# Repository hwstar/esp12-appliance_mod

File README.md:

**esp12-appliance_mod**
==========
This is a hardware implementation for my ESP8266-MQTT-io-node project.

**Features:**

Provides one bistable latching relay channel. Connectors are provided for a link LED and a local button to latch and unlatch the relay.
A dual voltage isolated power supply mounts over the top of the latching relay. The relay is capable of switching  a 16 Amp resistive load at 250VAC, or
a 20 Amp resistive load at 125VAC. See relay data sheet for further details. There are screw terminals for attaching the AC wiring  at the rear of the board (behind the power supply).

**EDA Software**

This board was designed using KICAD. 

**Board Size**

10cm x 10cm

**Board Blank Availability**

Board Blanks are available on Tindie:

https://www.tindie.com/products/hwstarsr/board-blank-for-esp12-appliancemod

**Firmware**

The firmware for this project can be found here:

https://github.com/hwstar/ESP8266-MQTT-io-node

**LICENSE**

Creative Commons Attribution Share-Alike license. (CC-BY-SA)

**Disclaimer**

Build and use at your own risk. This board design uses lethal mains voltages. I will not be responsible for any damages including but not limited to: errors or omissions, loss of life, or property damage. You have been warned.

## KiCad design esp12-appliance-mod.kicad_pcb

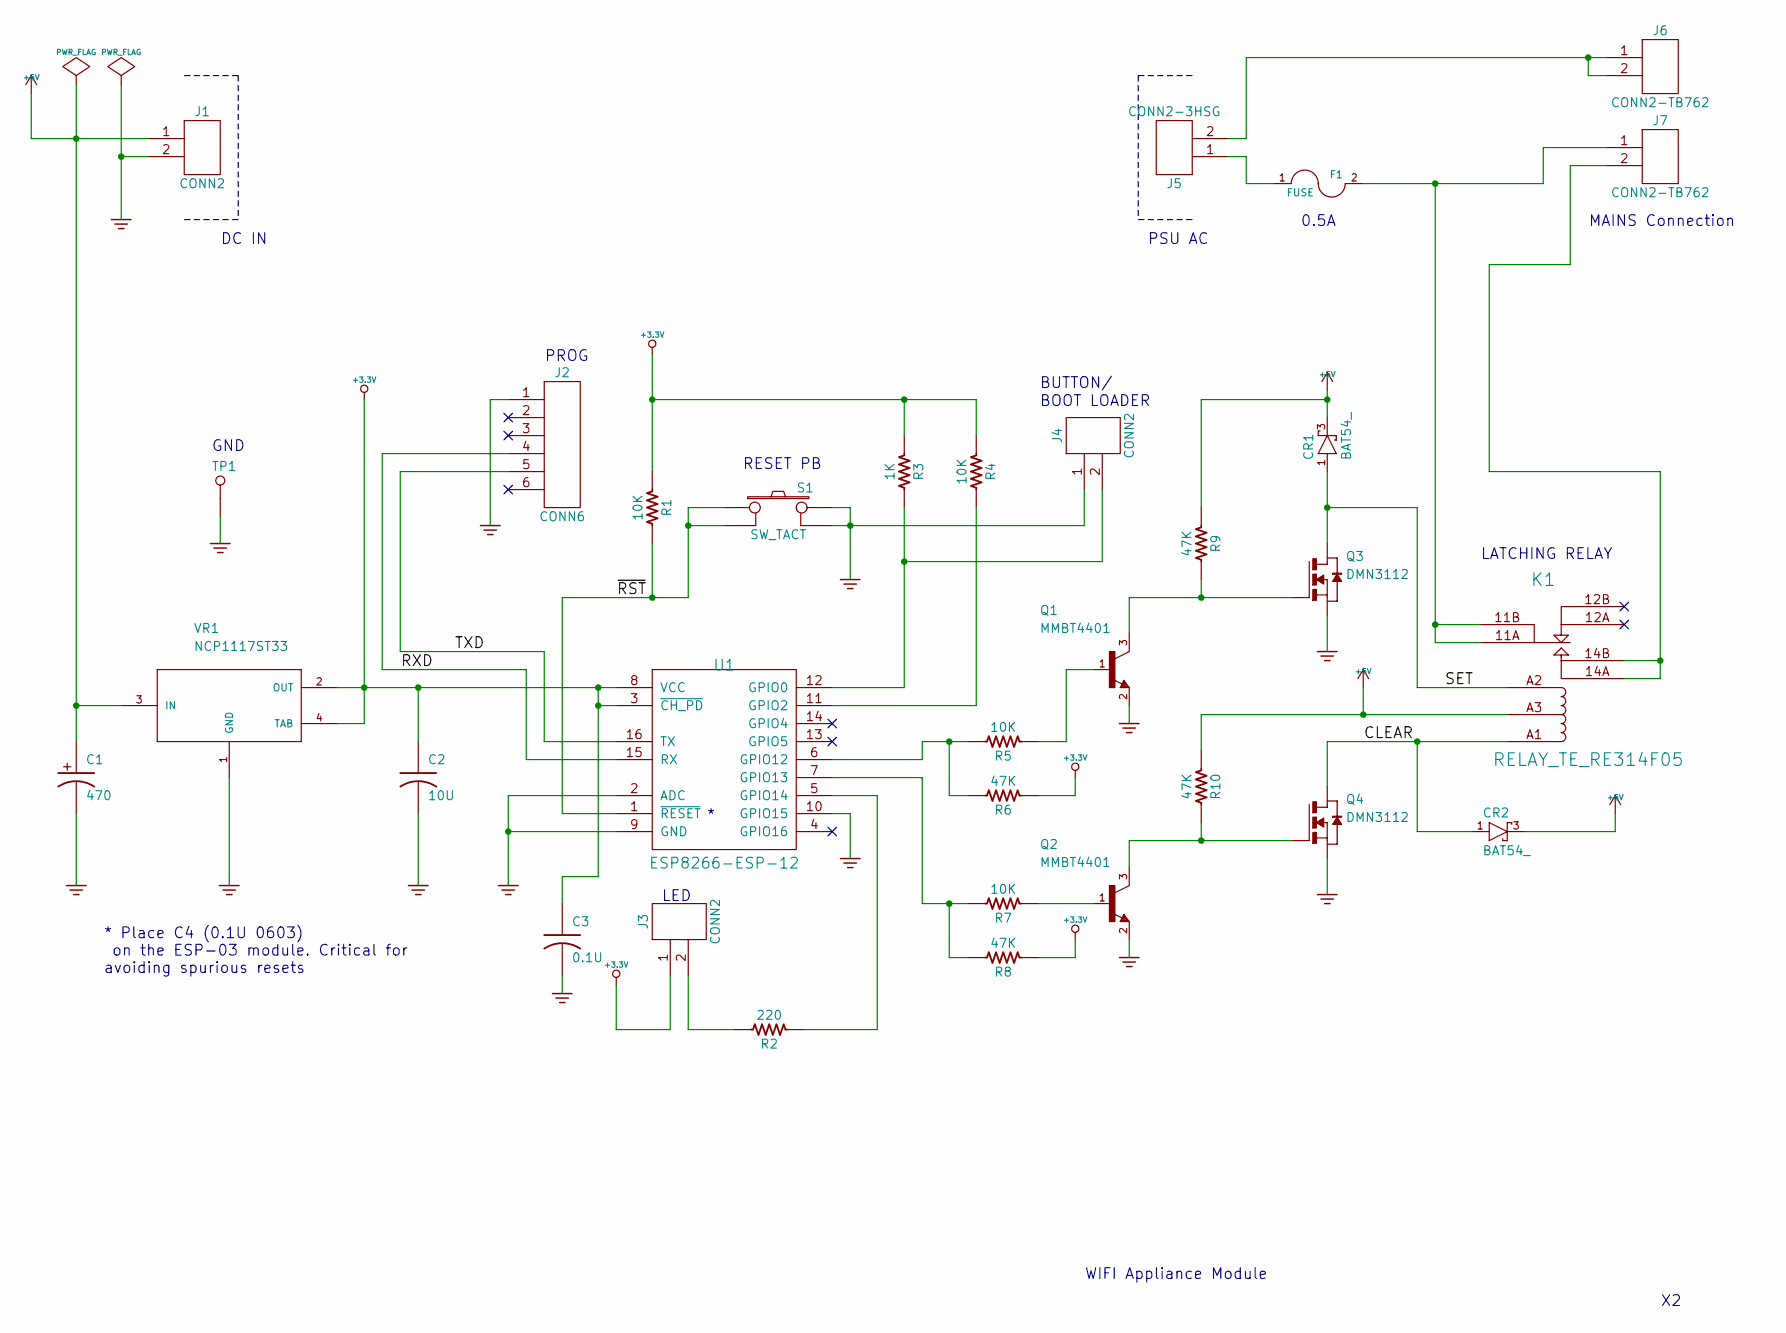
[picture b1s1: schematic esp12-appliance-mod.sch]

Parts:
C1: 470; PartNumber 800126-477
C2: 10U; CC0805; PartNumber 800003-106
C3: 0.1U; PartNumber 800000-104
CR1, CR2: BAT54_; SOT23; PartNumber 800127-101
F1: FUSE; PartNumber 800125-500
J1, J3, J4: CONN2; PartNumber 800114-102
J2: CONN6; PartNumber 800116-106
J5: CONN2-3HSG; PartNumber 800124-101
J6, J7: CONN2-TB762; PartNumber 800129-102
K1: RELAY_TE_RE314F05; PartNumber 800128-101
Q1, Q2: MMBT4401; SOT23; PartNumber 800110-101
Q3, Q4: DMN3112; SOT23; PartNumber 800123-101
R1, R4, R5, R7: 10K; RC0603; PartNumber 800010-103
R2: 220; RC0805; PartNumber 800011-221
R3: 1K; RC0603; PartNumber 800010-102
R6, R8, R9: 47K; RC0603; PartNumber 800010-473
R10: 47K; RC0603
S1: SW_TACT; PartNumber 800107-101
TP1: TESTPINTPSQ025; TESTPINSQ025
U1: ESP8266-ESP-12; PartNumber 800106-101
VR1: NCP1117ST33; SOT223; PartNumber 800121-101

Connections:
+3.3V: C2.1, C3.1, J3.1, R1.1, R3.1, R4.1, R6.1, R8.1, U1.3 (~CH_PD), U1.8 (VCC), VR1.2 (OUT), VR1.4 (TAB)
+5V: C1.1, CR1.3 (C), CR2.3 (C), J1.1, K1.A3, R9.1, R10.1, VR1.3 (IN)
/CLEAR: CR2.1 (A), K1.A1 (RESET), Q4.3 (D)
/RXD: J2.4, U1.15 (RX)
/SET: CR1.1 (A), K1.A2 (SET), Q3.3 (D)
/TXD: J2.5, U1.16 (TX)
/~RST: R1.2, S1.1, S1.2, U1.1 (~RESET)
GND: C1.2, C2.2, C3.2, J1.2, J2.1, J4.1, Q1.2 (E), Q2.2 (E), Q3.2 (S), Q4.2 (S), S1.3, S1.4, TP1.1, U1.2 (ADC), U1.9 (GND), U1.10 (GPIO15), VR1.1 (GND)
unnamed: F1.1, J5.1
unnamed: F1.2, J7.1, K1.11A (C), K1.11B (C)
unnamed: J3.2, R2.2
unnamed: J4.2, R3.2, U1.12 (GPIO0)
unnamed: J5.2, J6.1, J6.2
unnamed: J7.2, K1.14A (NO), K1.14B (NO)
unnamed: Q1.1 (B), R5.1
unnamed: Q1.3 (C), Q3.1 (G), R9.2
unnamed: Q2.1 (B), R7.1
unnamed: Q2.3 (C), Q4.1 (G), R10.2
unnamed: R2.1, U1.5 (GPIO14)
unnamed: R4.2, U1.11 (GPIO2)
unnamed: R5.2, R6.2, U1.6 (GPIO12)
unnamed: R7.2, R8.2, U1.7 (GPIO13)

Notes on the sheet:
RESET PB
BOOT LOADER
WIFI Appliance Module
LED
DC IN
0.5A
* Place C4 (0.1U 0603) on the ESP-03 module. Critical for avoiding spurious resets
MAINS Connection
PSU AC
BUTTON/
PROG
LATCHING RELAY
GND

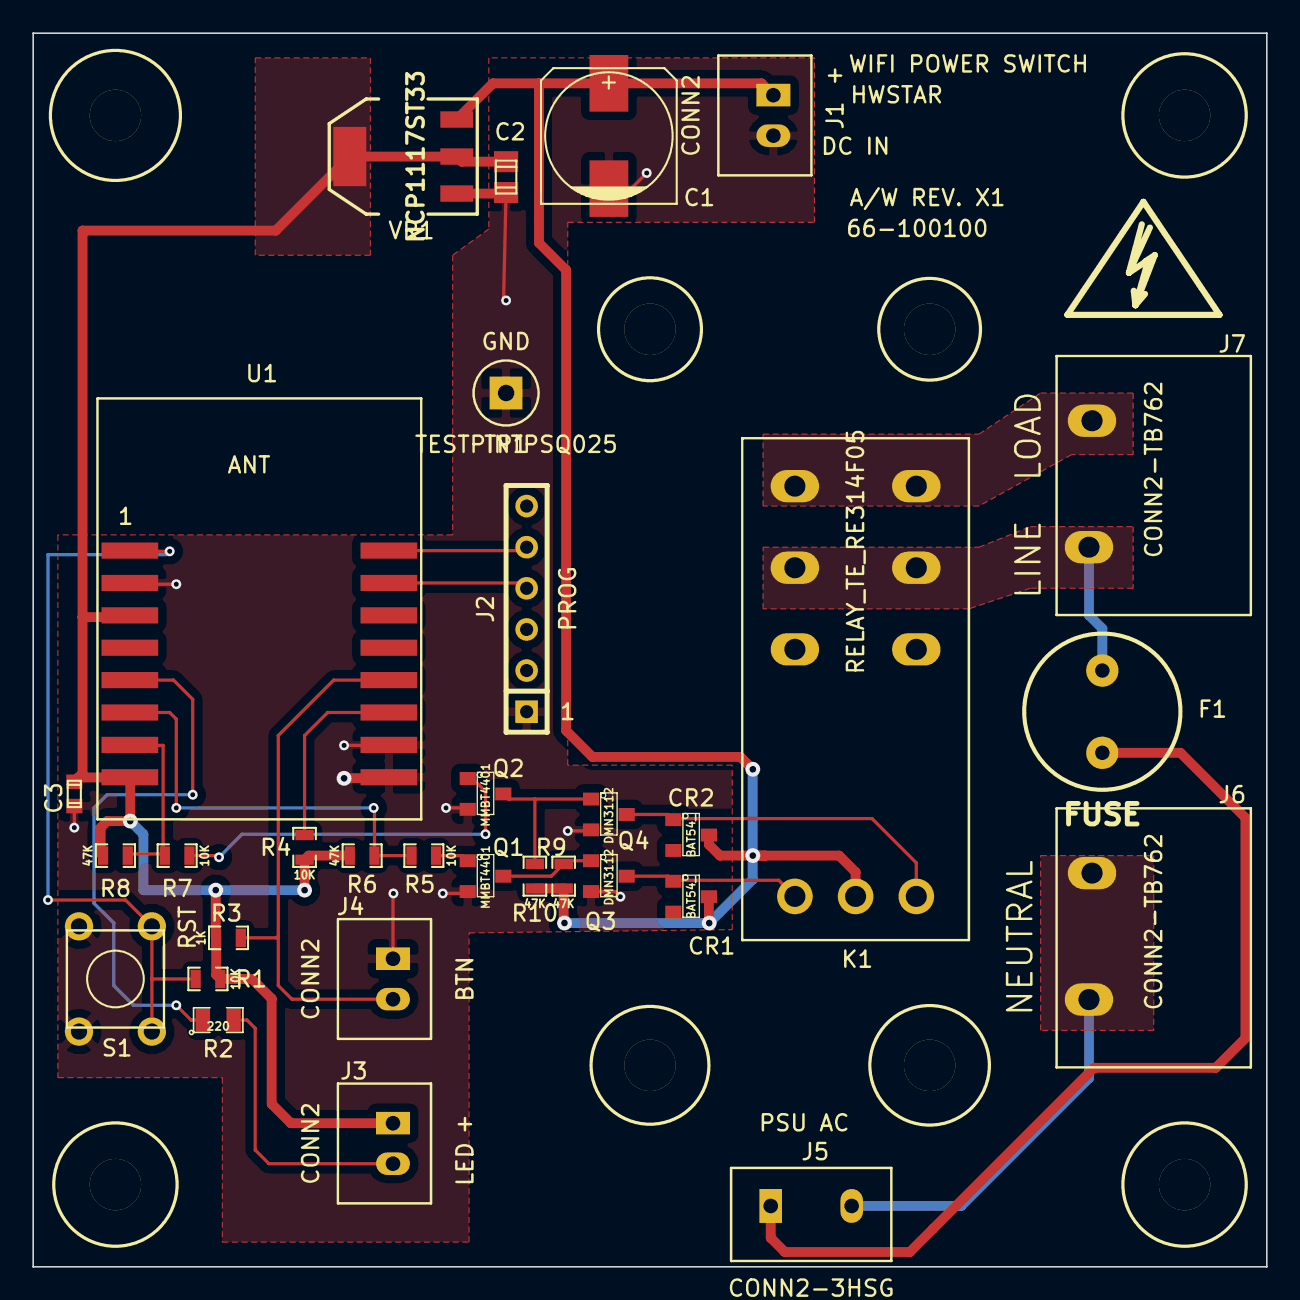
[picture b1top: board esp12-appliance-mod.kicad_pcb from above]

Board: 2 copper layers, 76.2 x 76.2 mm, 41 parts (0 on the bottom side), 22 nets.

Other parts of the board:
MTGHOLE125, MTGHOLE125#2, MTGHOLE125#3, MTGHOLE125#4, MTGHOLE125#5, MTGHOLE125#6, MTGHOLE125#7, MTGHOLE125#8: VAL**; MTGHOLE125
Sym: Symbol_HighVoltage_Type2_SilkTop_VerySmall

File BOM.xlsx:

Item | Qty | Meas | Reference | Description | Manufacturer | Part Number | Source | Notes
1 | 1 | ea | C1 | CAP, ELECT, 470uf/16V | Open Market |  | Ebay | 8mm x 8mm
2 | 1 | ea | C2 | CAP, 0805, X5R, 10uf/16V | Murata | GRM21BR161C106KE15L | Digi-Key | Or equivalent part
3 | 2 | ea | C3,C4 | CAP, 0603, X7R, 0.1uf/25V | Murata | GRM188R71E104KA01D | Digi-Key | Or equivalent part
4 | 2 | ea | CR1,CR2 | DIODE, GP, SHOTTKY, SOT23 | Open Market | BAT54 | Ebay | Cathode on pin 3, anode on pin 1
6 | 1 | ea | F1 | FUSE, 0.5A, SLO-BLOW, 8.5 X 8 MM | Littelfuse/Wickmann | 3720500 | Digi-Key
6 | 3 | ea | J1,J3,J4 | CONN, HDR, XH, 2 CKT | Open Market |  | Ebay | JST XH series knockoff*
7 | 1 | ea | J2 | CONN, HDR, BERGSTRIP, 6 POS, 0.1 IN PITCH | Open Market |  | Ebay | Breakable headers can be used
8 | 1 | ea | J5 | CONN, HDR, XH, 3 CKT | Open Market |  | Ebay | JST XH series knockoff*. Remove center pin.
9 | 2 | ea | J6,J7 | CONN, TERM BLK, 2 POS, 7.62MM PITCH | Open Market | KF7.62-2P | Ebay 231260624408
10 | 1 | ea | K1 | RELAY, 5V, LATCHING, SPDT, DUAL COIL, 16A, 250V | TE/SCHRACK | 8-1393239-5 | Ebay 361282277725 | Product code RT314F05
11 | 2 | ea | Q1,Q2 | XSTR, NPN, GP, SOT23 | Open Market | MMBT4401 | Ebay
12 | 2 | ea | Q3,Q4 | XSTR, MOSFET, N-CH, 30V | Vishay | Si2306BDS | Digi-Key
13 | 4 | ea | R1,R4,R5,R7 | RES,0603,10K,5% | Open Market |  | Ebay
14 | 1 | ea | R2 | RES,0805, 220, 5% | Open Market |  | Ebay
15 | 1 | ea | R3 | RES,0603,1K,5% | Open Market |  | Ebay
16 | 4 | ea | R6,R8,R9,R10 | RES,0603,47K,5% | Open Market |  | Ebay
17 | 1 | ea | S1 | SWITCH, TACT,6MM | Open Market |  | Ebay
18 | 1 | ea | TP1 | CONN, HDR, BERGSTRIP, 1 POS | Open Market |  | Ebay | Breakable headers can be used
19 | 1 | ea | U1 | MODULE, WIFI, ESP8266, ESP12 | Open Market | ESP12 | Ebay
20 | 1 | ea | VR1 | IC, VREG, LDO, 3.3V, SOT223 | NCP1117ST33T3G | On Semiconductor | Digi-Key
 |  |  | Power supply sub assembly
1 | 1 | ea | PSU | PSU, 5V, 1A, UNIV INPUT, ISOLATED | Open Market |  | Ebay 351211320656 | see picture, hole pattern must match main board.
2 | 1 | ea |  | CONN, PLUG 3 POS | Open Market |  | Ebay | JST XH series knockoff*
3 | 1 | ea |  | CONN, PLUG 2 POS | Open Market |  | Ebay | JST XH series knockoff*
4 | 4 | ea |  | CONTACT, JST XH SERIES | Open Market |  | Ebay | JST XH series knockoff*
5 | 0.001 | ft |  | WIRE, 24 AWG, UL 1007 | Open Market |  | Ebay
6 | 4 | ea |  | Nylon Standoff M2 20mm | Open Market |  | Ebay
7 | 4 | ea |  | Nylon Nut M2 | Open Market |  | Ebay
8 | 4 | ea |  | Nylon Screw M2 6mm | Open Market |  | Ebay
 | * |  | A small kit of JST XH compatible
 |  |  | connectors is available on Ebay
 |  |  | under item 141292096528
 |  |  | This will have all of the headers
 |  |  | pins and housings you need
 |  |  | to build the project.

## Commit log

2015-05-06 Initial checkin
2015-05-06 Add disclaimer
2015-05-06 Modify disclaimer
2015-05-06 Add license
2015-05-06 Cleanup. Add note about terminal blocks
2015-05-06 Remove extraneous word
2015-05-07 Update readme, add cache-lib file
2015-05-07 Update BOM with Ebay items numbers for critical parts
2015-06-03 Board size is 10cm X 10cm
2015-06-23 Add part numbers to schematic. Regenerate BOM using BOMTools
2015-06-23 Update schematic
2015-06-26 Fix BOM error. Add capacitor C4.
2015-06-26 Add capacitor C4 which goes between the ESP12 reset pin and the ESP12 case.
